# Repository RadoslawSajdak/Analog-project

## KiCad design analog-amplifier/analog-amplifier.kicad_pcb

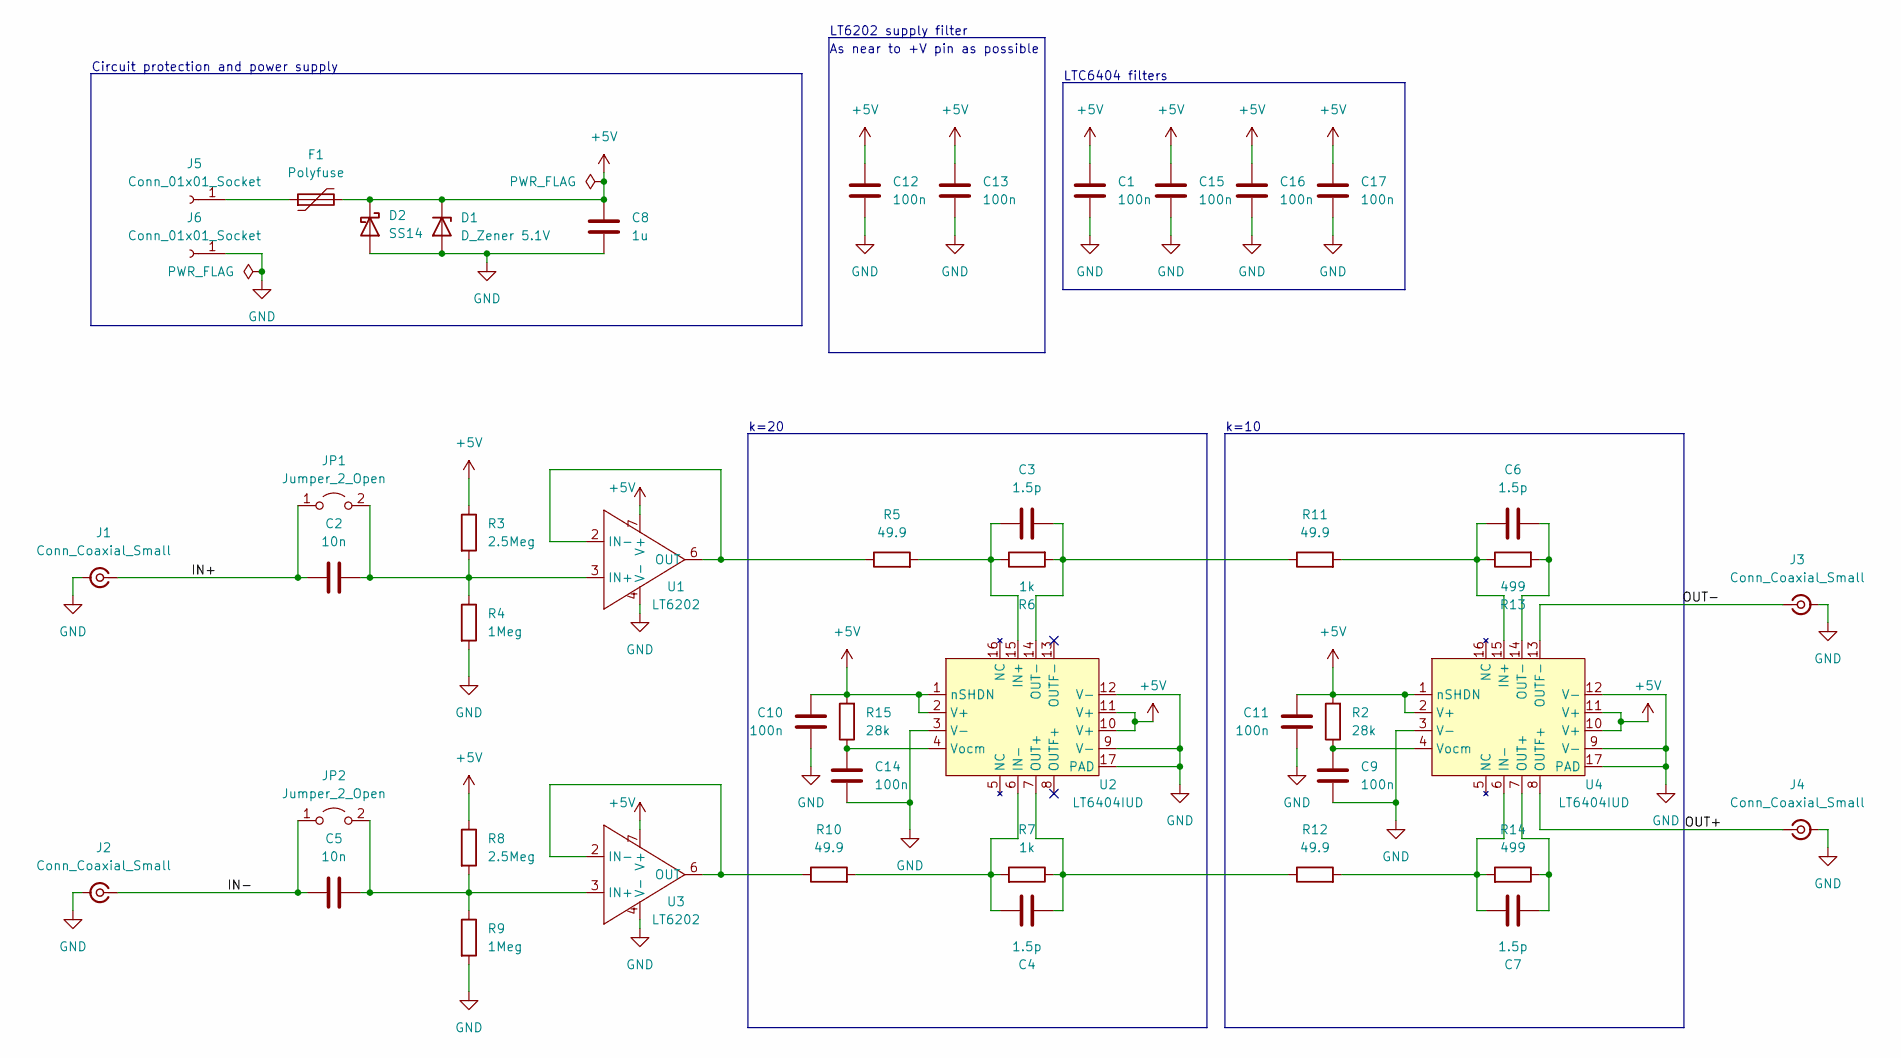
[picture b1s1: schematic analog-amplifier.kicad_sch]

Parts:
C1, C9, C10, C11, C12, C13, C14, C15, C16, C17: 100n; C_0603_1608Metric
C2, C5: 10n; C_0603_1608Metric
C3, C4, C6, C7: 1.5p; C_0603_1608Metric
C8: 1u; C_0805_2012Metric
D1: D_Zener 5.1V; SOT-23-3; LCSC C236173
D2: SS14; D_SMA; LCSC C2480
F1: Polyfuse; R_0603_1608Metric; LCSC C883092
J1, J2, J3, J4: Conn_Coaxial_Small; SMA_Samtec_SMA-J-P-X-ST-EM1_EdgeMount
J5, J6: Conn_01x01_Socket; PinSocket_1x01_P2.54mm_Vertical
JP1, JP2: Jumper_2_Open; PinSocket_1x02_P2.54mm_Vertical
R2, R15: 28k; R_0603_1608Metric
R3, R8: 2.5Meg; R_0603_1608Metric
R4, R9: 1Meg; R_0603_1608Metric
R5, R10, R11, R12: 49.9; R_0603_1608Metric; LCSC C23185
R6, R7: 1k; R_0603_1608Metric; LCSC C21190
R13, R14: 499; R_0603_1608Metric
U1, U3: LT6202; SO-8_3.9x4.9mm_P1.27mm; LCSC C672942
U2, U4: LT6404IUD; QFN-16-1EP_3x3mm_P0.5mm_EP1.45x1.45mm

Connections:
+5V: C1.1, C8.1, C10.1, C11.1, C12.1, C13.1, C15.1, C16.1, C17.1, D1.1 (K), D2.1 (K), F1.2, R2.2, R3.1, R8.1, R15.2, U1.7 (V+), U2.1 (nSHDN), U2.2 (V+), U2.10 (V+), U2.11 (V+), U3.7 (V+), U4.1 (nSHDN), U4.2 (V+), U4.10 (V+), U4.11 (V+)
/IN+: C2.1, J1.1 (In), JP1.1 (A)
/IN-: C5.1, J2.1 (In), JP2.1 (A)
/OUT+: J4.1 (In), U4.8 (OUTF+)
/OUT-: J3.1 (In), U4.13 (OUTF-)
GND: C1.2, C8.2, C9.1, C10.2, C11.2, C12.2, C13.2, C14.1, C15.2, C16.2, C17.2, D1.2 (A), D2.2 (A), J1.2 (Ext), J2.2 (Ext), J3.2 (Ext), J4.2 (Ext), J6.1, R4.2, R9.2, U1.4 (V-), U2.3 (V-), U2.9 (V-), U2.12 (V-), U2.17 (PAD), U3.4 (V-), U4.3 (V-), U4.9 (V-), U4.12 (V-), U4.17 (PAD)
unnamed: F1.1, J5.1
unnamed: C2.2, JP1.2 (B), R3.2, R4.1, U1.3 (IN+)
unnamed: C5.2, JP2.2 (B), R8.2, R9.1, U3.3 (IN+)
unnamed: R5.1, U1.2 (IN-), U1.6 (OUT)
unnamed: C3.2, R5.2, R6.1, U2.15 (IN+)
unnamed: C4.1, R7.2, R10.2, U2.6 (IN-)
unnamed: C4.2, R7.1, R12.1, U2.7 (OUT+)
unnamed: C3.1, R6.2, R11.1, U2.14 (OUT-)
unnamed: C14.2, R15.1, U2.4 (Vocm)
unnamed: R10.1, U3.2 (IN-), U3.6 (OUT)
unnamed: C6.2, R11.2, R13.1, U4.15 (IN+)
unnamed: C7.1, R12.2, R14.2, U4.6 (IN-)
unnamed: C7.2, R14.1, U4.7 (OUT+)
unnamed: C6.1, R13.2, U4.14 (OUT-)
unnamed: C9.2, R2.1, U4.4 (Vocm)

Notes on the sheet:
LTC6404 filters
As near to +V pin as possible
k=10
Circuit protection and power supply
LT6202 supply filter
k=20

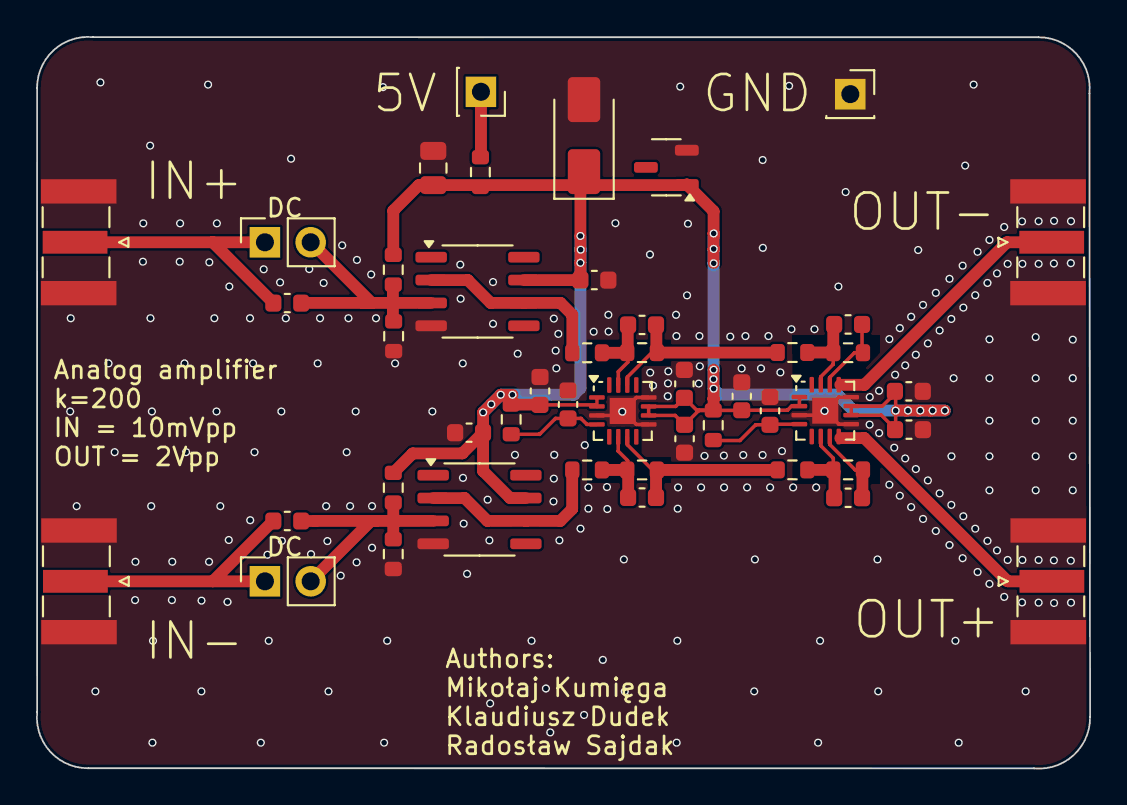
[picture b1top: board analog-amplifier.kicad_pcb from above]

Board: 2 copper layers, 58.5 x 40.6 mm, 46 parts (0 on the bottom side), 21 nets.

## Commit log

2024-11-02 Initial commit for the analog amplifier
2024-11-20 Prototype schematics
2024-11-20 Added simulation file
2024-11-21 Draft of the layout
2024-11-23 Finished Beta
2024-11-23 Added gerbers
2024-12-06 Updated simulation file with circuit png
